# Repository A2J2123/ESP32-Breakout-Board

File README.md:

# ESP32 Breakout Board

A simple breakout board for the ESP32, designed in KiCad as a quick guide to PCB design and prototyping.

## Overview

This project provides a straightforward, easy-to-assemble breakout board for the ESP32 microcontroller. It's intended for anyone interested in learning PCB design, prototyping, or working with the ESP32 platform.

## Features

- Designed with KiCad, a popular open-source PCB design tool
- Breaks out all essential ESP32 pins for easy prototyping
- Compact and beginner-friendly layout

## Images

### Schematic

### 2D Model

### 3D Model

## Getting Started

1. Download the KiCad project files from this repository.
2. Open the project in KiCad to view or modify the schematic and PCB layout.
3. Export Gerber files for manufacturing if you wish to fabricate the PCB.

---

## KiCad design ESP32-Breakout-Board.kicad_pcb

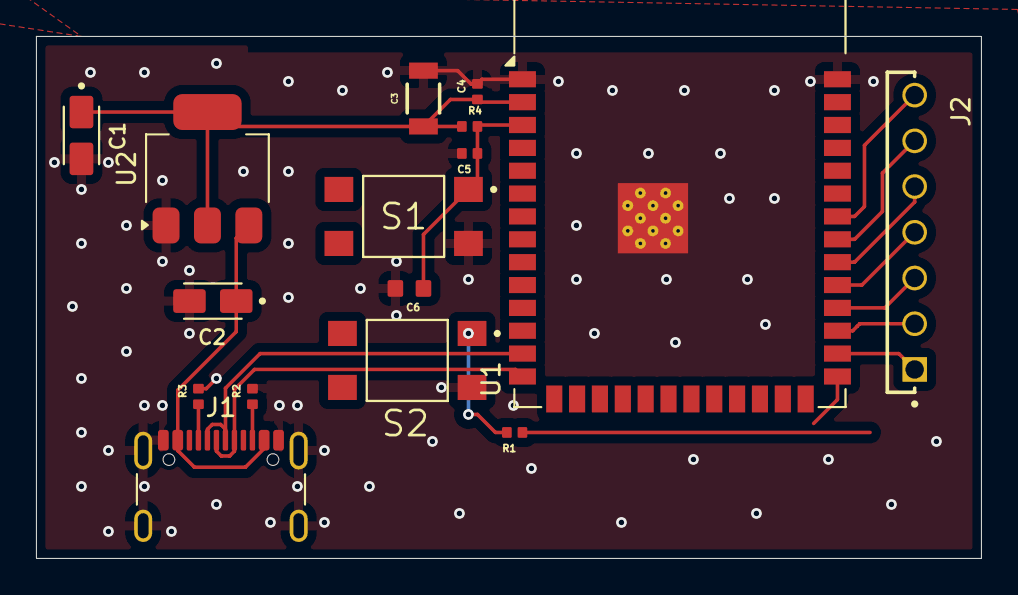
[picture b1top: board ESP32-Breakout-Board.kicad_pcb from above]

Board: 2 copper layers, 52.5 x 29.0 mm, 16 parts (0 on the bottom side), 17 nets.

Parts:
C1: TAJA226K010RNJ; CAPMP3216X180N
C2: TAJA106M010RNJ; CAPMP3216X180N
C3: WCAP-CSGP_1206_H1.6
C4, C5: CL05B104KP5VPNC; CAPC1005X55N
C6: CL10B105KP8NNNC; CAPC1608X90N
J1: USB_C_Receptacle_USB2.0_16P; USB_C_Receptacle_GCT_USB4105-xx-A_16P_TopMnt_Horizontal
J2: Conn_01x08_MountingPin; SAMTEC_MTSW-107-08-T-S-190-NA
R1: 100; CAPC1005X55N
R2, R3: 5.1k; CAPC1005X55N
R4: 10k; CAPC1005X55N
S1, S2: TL3305CF160QG; SW_TL3305CF160QG
U1: ESP32-S3-WROOM-1
U2: AMS1117-3.3; SOT-223-3_TabPin2

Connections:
+3V3: C1.1, C3.1, C4.1, R4.1, U1.2 (3V3), U2.2 (VO)
+5V: C2.1, J1.A4 (VBUS), J1.A9 (VBUS), J1.B4 (VBUS), J1.B9 (VBUS), U2.3 (VI)
BOOT: R1.1, U1.27 (IO0)
D+: J1.A6 (D+), J1.B6 (D+), U1.14 (USB_D+)
D-: J1.A7 (D-), J1.B7 (D-), U1.13 (USB_D-)
EN: C5.1, C6.1, R4.2, S1.1, U1.3 (EN)
GND: C1.2, C2.2, C3.2, C4.2, C5.2, C6.2, J1.A1 (GND), J1.A12 (GND), J1.B1 (GND), J1.B12 (GND), J1.S1 (SHIELD), R2.2, R3.2, S1.3, S2.3, U1.1 (GND), U1.40 (GND), U1.41 (GND), U2.1 (GND)
unnamed: J1.A5 (CC1), R3.1
unnamed: J1.B5 (CC2), R2.1
unnamed: J2.01 (Pin_1), U1.28 (IO35)
unnamed: J2.02 (Pin_2), U1.29 (IO36)
unnamed: J2.03 (Pin_3), U1.30 (IO37)
unnamed: J2.04 (Pin_4), U1.31 (IO38)
unnamed: J2.05 (Pin_5), U1.32 (IO39)
unnamed: J2.06 (Pin_6), U1.33 (IO40)
unnamed: J2.07 (Pin_7), U1.34 (IO41)
unnamed: R1.2, S2.1

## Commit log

2025-09-09 Initial Commit with completed project
2025-09-09 Adding ReadMe file describing project
2025-09-15 Updated project images
